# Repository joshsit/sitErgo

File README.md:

# Compact Ergonomic Mechanical Keyboard (sitErgo)

A custom-designed, compact mechanical keyboard prototype focused on ergonomics, portability, and efficient typing.  
Developed as an independent engineering project exploring human factors, mechanical design, and open-source firmware customization.

*Prototype v1 of the sitErgo Keyboard*

---

## Motivation & Background
Most mainstream keyboards follow a legacy layout that can contribute to poor posture, finger strain, and inefficiency.  
This project explores an alternative design: a **compact, column-staggered, ergonomic mechanical keyboard** that balances usability with portability.  
Inspired by enthusiast boards like the **Corne, Atreus, and Alice layouts**, this keyboard experiments with features such as:
- Columnar stagger for natural finger alignment  
- Inverted-V orientation to reduce ulnar deviation (wrist bending outward)  
- Support for alternative typing layouts (e.g., **Colemak-DH**)  
- Compact footprint for travel and desk efficiency  

---

## Features
- **Compact 40% layout** (fewer keys, layered functionality)  
- **Column-staggered design** for improved finger ergonomics  
- **Inverted-V orientation** for reduced ulnar deviation  
- **Open-source QMK firmware** with customizable layers, macros, and mouse keys  
- **Hot-swappable switches** for customizability  

---

## Bill of Materials (Prototype v1)
| Component                  | Example Part / Source          | Cost (Approx.) |
|----------------------------|--------------------------------|----------------|
| PCB (custom)               | JLCPCB fabrication             | <$5            |
| Microcontroller            | RP2040-Zero                    | <$5            |
| Hot-Swap Sockets (x36)     | MX style sockets               | <$5            |
| Diodes (1N4148, x36)       | Generic, through-hole diodes   | <$5            |
| Case / Plate (prototype)   | 3D printed PLA+                | <$5            |
| Misc. (fasteners, etc.)    | —                              | <$5            |
| Key switches (x36)         | Akko Pro v3 MX switches        | $10            |
| Keycaps (blank, x36)       | Generic MOA profile keycaps    | $10            |
| **Total**                  | —                              | ~$35           |

*(Costs vary depending on sourcing and materials; BOM provided for reference.)*

---

## Challenges & Lessons Learned
- Balancing **ergonomics vs. portability** (trade-offs between tenting, size, and bulk)  
- PCB design iteration for **diode placement and routing**  
- Firmware learning curve with **QMK keymap customization**  
- Adapting to alternative typing layouts (Colemak-DH)  

---

## Firmware & Layout
The keyboard runs on **QMK firmware**, allowing full customization of:  
- Layered layouts (base, function, navigation, numpad)  
- Mouse keys and media controls  
- Macros for coding/productivity  
- Support for **Colemak-DH** and standard layouts  

👉 See [firmware/](firmware) for keymaps, layout diagrams, and config files.  

---

## Future Work
- Refined PCB & plate design for durability  
- Case redesign for aesthetics + portability  
- Wireless (Bluetooth) support in future iterations  
- Broader keycap compatibility testing  

---

## Documentation
- 📄 [Full Project Report](docs/REPORT.md) *(detailed write-up with design considerations, market research, and lessons learned)*  
- 📷 [More Images](images/)  
- ⌨️ [Firmware & Keymaps](firmware/)  

---

## License
MIT License – open for hobbyist use and modification.

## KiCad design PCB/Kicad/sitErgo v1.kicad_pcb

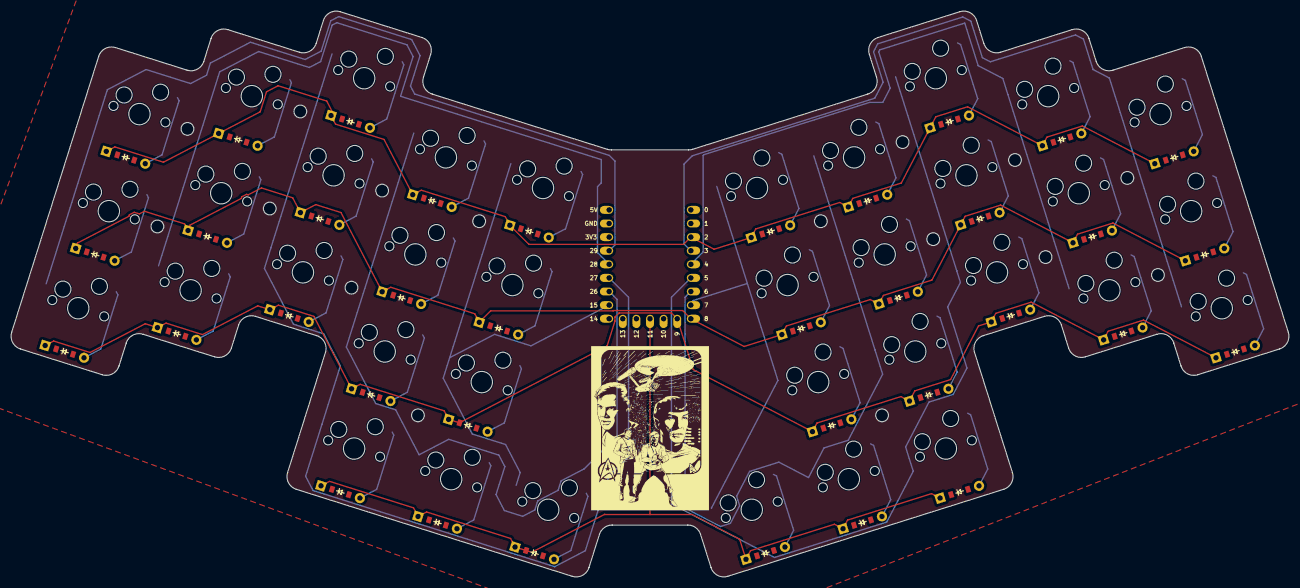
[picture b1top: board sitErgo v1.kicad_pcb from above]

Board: 2 copper layers, 238.6 x 105.6 mm, 73 parts (0 on the bottom side), 50 nets.

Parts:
D1, D2, D3, D4, D5, D6, D7, D8, D9, D10, D11, D12, D13, D14, D15, D16, D17, D18, D19, D20, D21, D22, D23, D24, D25, D26, D27, D28, D29, D30, D31, D32, D33, D34, D35, D36: ComboDiode
MCU1: RP2040_Zero
S1, S2, S3, S4, S5, S6, S7, S8, S9, S10, S11, S12, S13, S14, S15, S16, S17, S18, S19, S20, S21, S22, S23, S24, S25, S26, S27, S28, S29, S30, S31, S32, S33, S34, S35, S36: MX

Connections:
P2: D3.1, D6.1, D9.1, D12.1, D15.1, D21.1, D24.1, D27.1, D30.1, D33.1, MCU1.3
P3: MCU1.4, S19.1, S20.1, S21.1
P4: MCU1.5, S22.1, S23.1, S24.1
P5: MCU1.6, S25.1, S26.1, S27.1, S34.1
P6: MCU1.7, S28.1, S29.1, S30.1, S35.1
P7: MCU1.8, S31.1, S32.1, S33.1, S36.1
P8: D2.1, D5.1, D8.1, D11.1, D14.1, D20.1, D23.1, D26.1, D29.1, D32.1, MCU1.9
P9: D1.1, D4.1, D7.1, D10.1, D13.1, D19.1, D22.1, D25.1, D28.1, D31.1, MCU1.10
P11: D16.1, D17.1, D18.1, D34.1, D35.1, D36.1, MCU1.12
P15: MCU1.16, S13.1, S14.1, S15.1, S18.1
P26: MCU1.17, S10.1, S11.1, S12.1, S17.1
P27: MCU1.18, S7.1, S8.1, S9.1, S16.1
P28: MCU1.19, S4.1, S5.1, S6.1
P29: MCU1.20, S1.1, S2.1, S3.1
index_bottom: D10.2, S10.2
index_home: D11.2, S11.2
index_top: D12.2, S12.2
inner_bottom: D13.2, S13.2
inner_cluster: D16.2, S16.2
inner_home: D14.2, S14.2
inner_top: D15.2, S15.2
middle_bottom: D7.2, S7.2
middle_cluster: D17.2, S17.2
middle_home: D8.2, S8.2
middle_top: D9.2, S9.2
mirror_index_bottom: D28.2, S28.2
mirror_index_home: D29.2, S29.2
mirror_index_top: D30.2, S30.2
mirror_inner_bottom: D31.2, S31.2
mirror_inner_cluster: D34.2, S34.2
mirror_inner_home: D32.2, S32.2
mirror_inner_top: D33.2, S33.2
mirror_middle_bottom: D25.2, S25.2
mirror_middle_cluster: D35.2, S35.2
mirror_middle_home: D26.2, S26.2
mirror_middle_top: D27.2, S27.2
mirror_outer_cluster: D36.2, S36.2
mirror_pinky_bottom: D19.2, S19.2
mirror_pinky_home: D20.2, S20.2
mirror_pinky_top: D21.2, S21.2
mirror_ring_bottom: D22.2, S22.2
mirror_ring_home: D23.2, S23.2
mirror_ring_top: D24.2, S24.2
outer_cluster: D18.2, S18.2
pinky_bottom: D1.2, S1.2
pinky_home: D2.2, S2.2
pinky_top: D3.2, S3.2
ring_bottom: D4.2, S4.2
ring_home: D5.2, S5.2
ring_top: D6.2, S6.2

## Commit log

2025-08-21 adding documentation
2025-08-21 added pcb and cad files
